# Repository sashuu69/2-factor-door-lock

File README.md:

# 2 Factor Authenticated Door Lock

## Introduction

The 2 Factor door lock is a locking system built using Arduino UNO, LCD display, R307 fingerprint sensor and keypad.

## Folder Structure

1. docs/top-layer.png : PCB Board top Design
2. docs/bottom-layer.png : PCB Board bottom design
3. docs/drills.png : PCB Board drills design
4. eagle-design : PCB design
5. src : code

## Components Used

1. Switch (X1) - [Tomson Electronics](https://www.tomsonelectronics.com/products/6mm-x-6mm-x-5mm-micro-switch)
2. LED 0805 (x3) - [Digikey](https://www.digikey.in/catalog/en/partgroup/chipled-0805-rectangle-with-flat-top-leds/34905)
3. Pin header (x2) - [Robu](https://robu.in/product/adafruit-stacking-headers-for-feather-12-pin-and-16-pin-female-headers/)
4. Screw Terminal 1x2 (x1) - [Tomson Electronics](https://www.tomsonelectronics.com/products/2-pin-pcb-mount-screw-terminal-block-connectors-126)
5. Screw Terminal 1x4 (x1) - [Robu](https://robu.in/product/4-pin-5-08mm-pitch-pluggable-screw-terminal-block-pack-of-3/)
6. Capacitor 0805 100nF (x1) - [Robu](https://robu.in/product/100nf-0805-surface-mount-multilayer-ceramic-capacitor-pack-of-40/)
7. Resistor 0805 100Ω (x1) - [Tomson Electronics](https://www.tomsonelectronics.com/products/4-7-820-ohms-thick-film-chip-smd-resistors-0805?variant=37572045209795)
8. Resistor 0805 10KΩ (x3) - [Tomson Electronics](https://www.tomsonelectronics.com/products/1-240-kohms-thick-film-chip-smd-resistors-0805?variant=37572054515907)
9. Capacitor 175TMP-0810 10µF (x1) - [Tomson Electronics](https://www.mouser.in/ProductDetail/Lelon/VE-100M2ATR-0810?qs=GtPRU6UQL8zXzI3APMGIww==)
10. Resistor 0805 150Ω (x1) - [ELECTRONICScomp](https://www.electronicscomp.com/150-ohm-resistor-0805-smd-package)
11. Crystal 16Hz (x1) - [Tomson Electronics](https://www.tomsonelectronics.com/products/crystal-oscillator-16-mhz-small)
12. Resistor 0805 180Ω (x1) - [Tomson Electronics](https://www.tomsonelectronics.com/products/4-7-820-ohms-thick-film-chip-smd-resistors-0805?variant=37572045045955)
13. Resistor 0805 1KΩ (x7) - [Tomson Electronics](https://www.tomsonelectronics.com/products/1-240-kohms-thick-film-chip-smd-resistors-0805?variant=37572054548675)
14. Diode 1N4007 (x2) - [Tomson Electronics](https://www.tomsonelectronics.com/products/diode-1n-4007)
15. Capacitor 175TMP-0810 1µF (x1) - [Mouser](https://www.mouser.in/ProductDetail/Lelon/VZH-331M1ETR-0810?qs=sXzuR3ywNuchKJ7mmh%252BA6w==)
16. Resistor 0805 220Ω (x3) - [Tomson Electronics](https://www.tomsonelectronics.com/products/4-7-820-ohms-thick-film-chip-smd-resistors-0805?variant=37572044980419)
17. Capacitor 0805 22pF (x1) - [Tomson Electronics](https://robu.in/product/22pf-0805-surface-mount-multilayer-ceramic-capacitor-pack-of-50/)
18. Resistor 0805 330Ω (x1) - [Tomson Electronics](https://www.tomsonelectronics.com/products/4-7-820-ohms-thick-film-chip-smd-resistors-0805?variant=37572045111491)
19. Resistor 0805 390Ω (x1) - [KTRON](https://www.ktron.in/product/resistor-390-ohms-5-1-8w-smd-0805/)
20. Capacitor 175TMP-0810 470µF (x1) - [Element14](https://in.element14.com/c/passive-components/capacitors/aluminium-electrolytic-capacitors/smd-aluminium-electrolytic-capacitors?capacitance=470uf)
21. Resistor 0805 510Ω (x1) - [Tomson Electronics](https://www.tomsonelectronics.com/products/4-7-820-ohms-thick-film-chip-smd-resistors-0805?variant=37572044914883)
22. Resistor 0805 680Ω (x1) - [ELECTRONICScomp](https://www.electronicscomp.com/680-ohm-resistor-0805-smd-package)
23. 7805T (x1) - [Tomson Electronics](https://www.tomsonelectronics.com/products/regulator-ic-7805)
24. Resistor 0805 82Ω (x1) - [KTRON](https://www.ktron.in/product/resistor-82-ohms-51-8w-smd-0805/)
25. ATMEGA328P-AU (x1) - [Tomson Electronics](https://www.tomsonelectronics.com/products/smd-ic-atmega-328?variant=49936455955)
26. BC547 (x1) - [Tomson Electronics](https://www.tomsonelectronics.com/products/transistor-bc-547)
27. Barrel Jack (x1) - [Tomson Electronics](https://www.tomsonelectronics.com/products/dc-barrel-power-jack)
28. PCF8574AT (x1) - [Mouser](https://www.mouser.in/ProductDetail/NXP-Semiconductors/PCF8574AT-3518?qs=LOCUfHb8d9s1dE4yk7F8TQ%3D%3D)
29. 5V Relay (x1) - [Tomson Electronics](https://www.tomsonelectronics.com/products/5v-single-contact-sugar-cube-relay)
30. 16x2 LCD Display (x1) - [Tomson Electronics](https://www.tomsonelectronics.com/products/16x1-character-green-backlight-lcd-display)

## PCB Design

### Top Layer

### Bottom Layer

### Drills Design

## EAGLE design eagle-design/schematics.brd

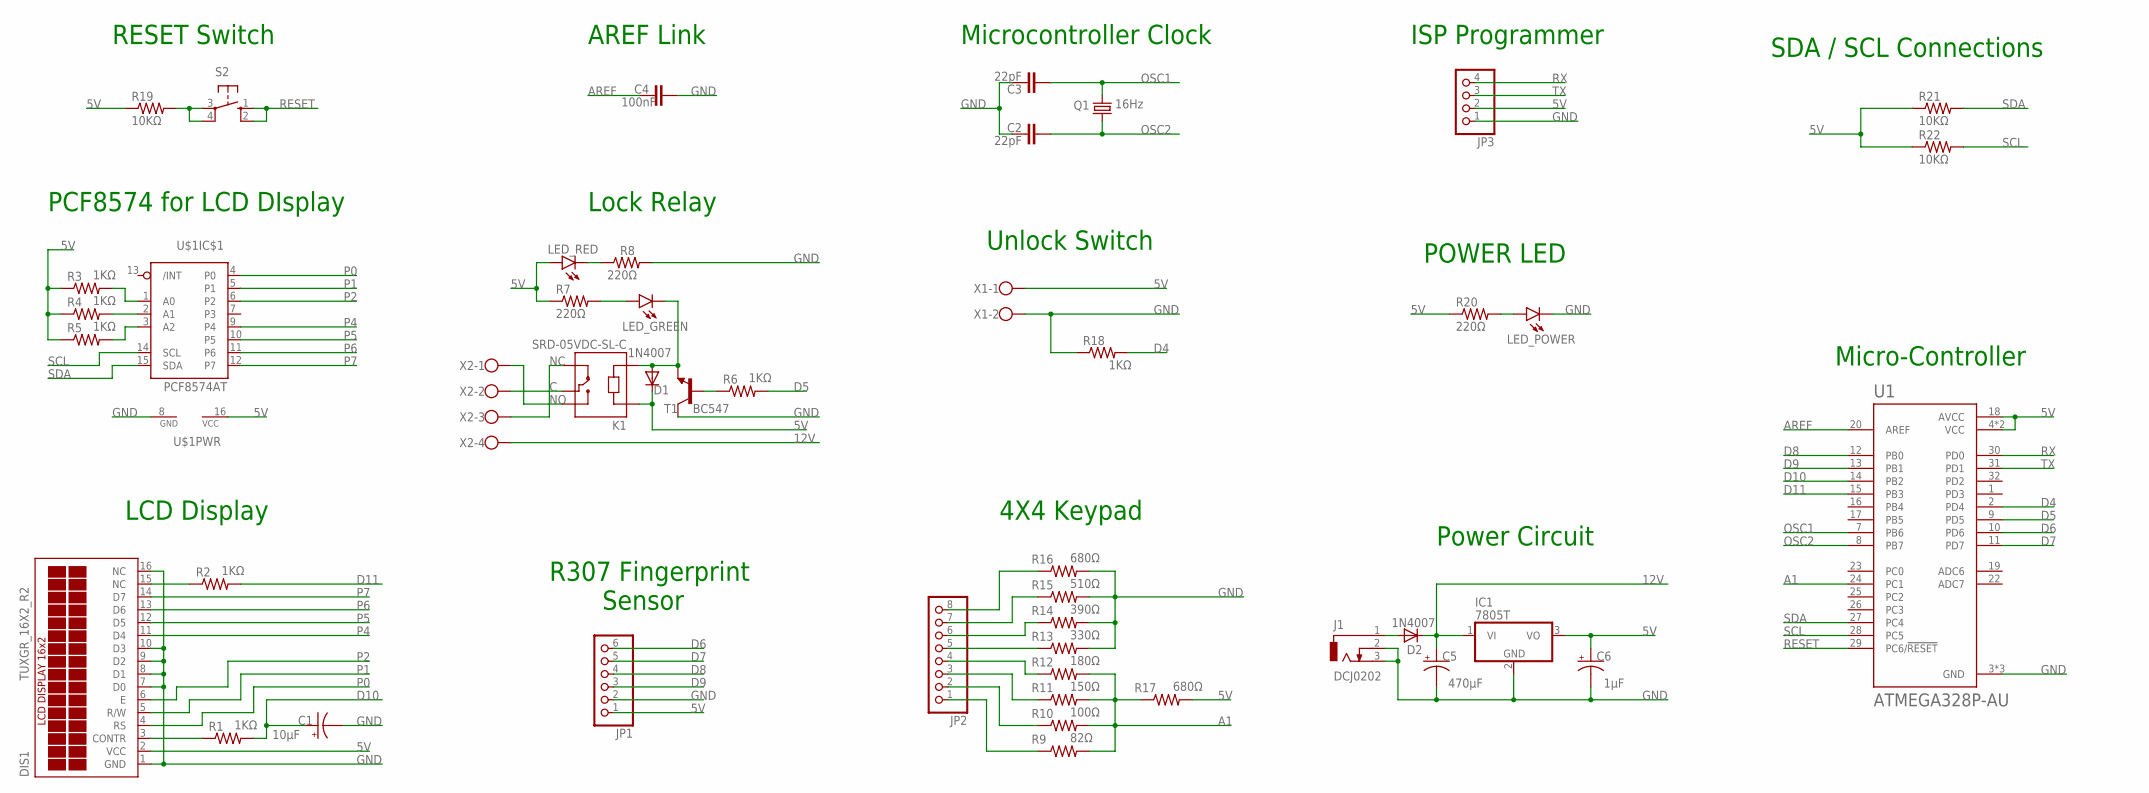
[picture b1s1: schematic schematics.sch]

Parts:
C1: 10µF; 175TMP-0810
C2, C3: 22pF; C0805
C4: 100nF; C0805
C5: 470µF; 175TMP-0810
C6: 1µF; 175TMP-0810
D1, D2: 1N4007; SMA
DIS1: TUXGR_16X2_R2
IC1: 7805T; TO220H
J1: DCJ0202
JP1: PINHD-1X6; 1X06
JP2: PINHD-1X8; 1X08
JP3: PINHD-1X4; 1X04
K1: SRD-05VDC-SL-C; RELAY_SRD-05VDC-SL-C
LED_GREEN: LEDCHIPLED_0805; CHIPLED_0805
LED_POWER: LEDCHIPLED_0805; CHIPLED_0805
LED_RED: LEDCHIPLED_0805; CHIPLED_0805
Q1: 16Hz; HC49/S
R1, R2, R3, R4, R5, R6, R18: 1KΩ; R0805
R7, R8, R20: 220Ω; R0805
R9: 82Ω; R0805
R10: 100Ω; R0805
R11: 150Ω; R0805
R12: 180Ω; R0805
R13: 330Ω; R0805
R14: 390Ω; R0805
R15: 510Ω; R0805
R16, R17: 680Ω; R0805
R19, R21, R22: 10KΩ; R0805
S2: 10-XX; B3F-10XX
T1: BC547; TO92
U1: ATMEGA328P-AU; QFP80P900X900X120-32N
U$1: PCF8574AT; SO16
X1: W237-102
X2: W237-4

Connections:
5V: C6.+, D1.K (C), DIS1.2 (VCC), IC1.3 (VO), JP1.1, JP3.2, K1.A1, LED_RED.A, R3.1, R4.1, R5.1, R7.1, R17.2, R19.1, R20.1, R21.1, R22.1, U1.4 (VCC), U1.6 (VCC), U1.18 (AVCC), U$1.16 (VCC), X1.1
12V: C5.+, D2.K (C), IC1.1 (VI), X2.4
A1: R9.2, R10.2, R11.2, R12.2, R17.1, U1.24 (PC1)
AREF: C4.2, U1.20 (AREF)
C: K1.COM, X2.2
D4: R18.2, U1.2 (PD4)
D5: R6.2, U1.9 (PD5)
D6: JP1.6, U1.10 (PD6)
D7: JP1.5, U1.11 (PD7)
D8: JP1.4, U1.12 (PB0)
D9: JP1.3, U1.13 (PB1)
D10: C1.+, R1.2, U1.14 (PB2)
D11: R2.2, U1.15 (PB3)
GND: C1.-, C2.2, C3.2, C4.1, C5.-, C6.-, DIS1.1 (GND), DIS1.7 (D0), DIS1.8 (D1), DIS1.9 (D2), DIS1.10 (D3), DIS1.16 (NC), IC1.2 (GND), J1.2, J1.3, JP1.2, JP3.1, LED_POWER.C, R8.2, R13.2, R14.2, R15.2, R16.2, R18.1, T1.3 (C), U1.3 (GND), U1.5 (GND), U1.21 (GND), U$1.8 (GND), X1.2
unnamed: DIS1.3 (CONTR), R1.1
unnamed: R3.2, U$1.1 (A0)
unnamed: R4.2, U$1.2 (A1)
unnamed: DIS1.15 (NC), R2.1
unnamed: R5.2, U$1.3 (A2)
unnamed: D1.A, K1.A2, LED_GREEN.C, T1.1 (E)
unnamed: R6.1, T1.2 (B)
unnamed: LED_RED.C, R8.1
unnamed: LED_GREEN.A, R7.2
unnamed: JP2.8, R16.1
unnamed: JP2.7, R15.1
unnamed: JP2.6, R14.1
unnamed: JP2.5, R13.1
unnamed: JP2.4, R12.1
unnamed: JP2.3, R11.1
unnamed: JP2.2, R10.1
unnamed: JP2.1, R9.1
unnamed: R19.2, S2.3, S2.4 (P1)
unnamed: LED_POWER.A, R20.2
unnamed: D2.A, J1.1
NC: K1.NC, X2.3
NO: K1.NO, X2.1
OSC1: C3.1, Q1.2, U1.7 (PB6)
OSC2: C2.1, Q1.1, U1.8 (PB7)
P0: DIS1.4 (RS), U$1.4 (P0)
P1: DIS1.5 (R/W), U$1.5 (P1)
P2: DIS1.6 (E), U$1.6 (P2)
P4: DIS1.11 (D4), U$1.9 (P4)
P5: DIS1.12 (D5), U$1.10 (P5)
P6: DIS1.13 (D6), U$1.11 (P6)
P7: DIS1.14 (D7), U$1.12 (P7)
RESET: S2.1 (S), S2.2 (S1), U1.29 (PC6/!RESET)
RX: JP3.4, U1.30 (PD0)
SCL: R22.2, U1.28 (PC5), U$1.14 (SCL)
SDA: R21.2, U1.27 (PC4), U$1.15 (SDA)
TX: JP3.3, U1.31 (PD1)

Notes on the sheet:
LCD Display
PCF8574 for LCD DIsplay
R307 Fingerprint Sensor
Lock Relay
4X4 Keypad
Unlock Switch
RESET Switch
Microcontroller Clock
AREF Link
ISP Programmer
POWER LED
Power Circuit
Micro-Controller
SDA / SCL Connections

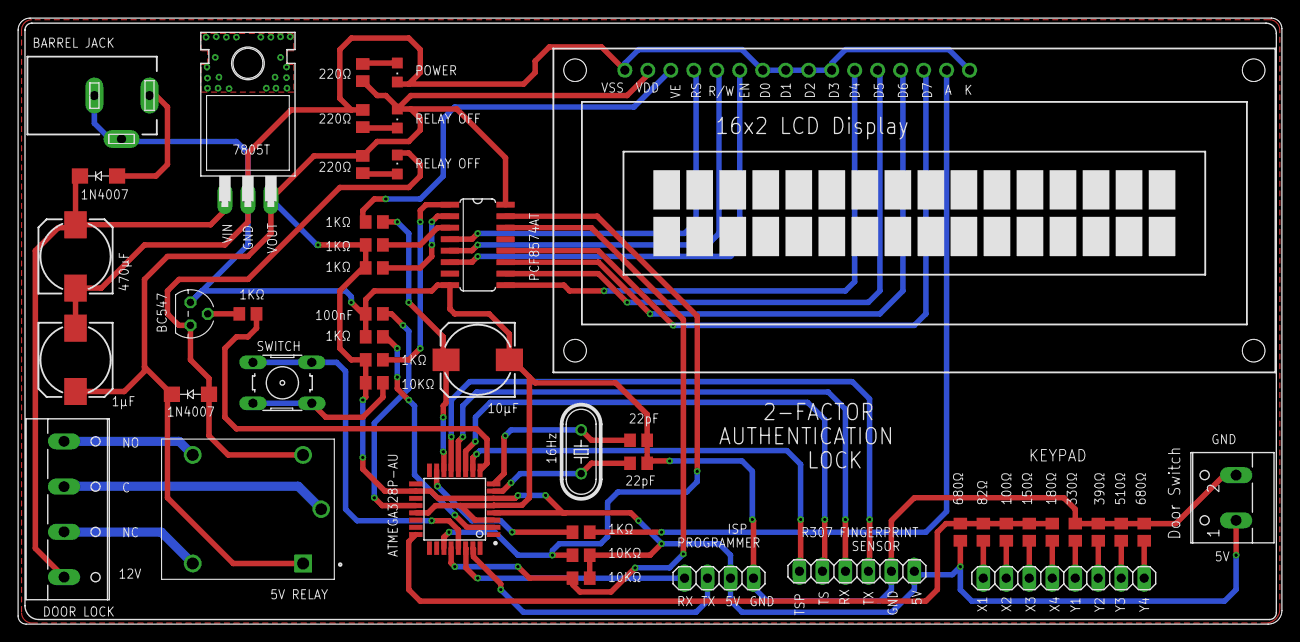
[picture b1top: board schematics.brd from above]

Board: 2 copper layers, 139.7 x 67.0 mm, 47 parts (0 on the bottom side), 50 nets.

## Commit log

2020-01-01 Added header files
2020-01-01 Fixed errors and commented the header files
2020-01-01 Completed version 1: All required features added
2020-01-02 Added comments
2020-01-03 new changes
2021-06-13 removed .DS_Store and added to gitignore
2021-06-13 Updated doc
2021-08-26 created new eagle schematics
2021-08-28 completed design
2021-08-28 Added exports and updated docs
2021-08-28 Added component list with links
2021-08-28 Added missing connection
2021-08-28 Added new exports
2022-05-03 Added PCB photos
2022-05-03 Image fix
